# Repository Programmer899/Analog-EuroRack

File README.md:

# Analog-EuroRack
### - Description
This is an analog eurorack where you can direct signals from one module to the next and by that, produce sound.
This ia a project I have been working on for a Music project for a thing called [Half Life](https://halflife.hackclub.com).
I wanted to do something interresting, a way that you could create your own unique sound rather than writing it with code.

### - What is the meaning
The meaning for this project is that you can redirect signals from different connections and in the end get your own uniquely modulated sound. Because I have tried to have it as a "EuroRack Format" it means that in the future if I keep working on this project, I could add more modulators such as low and high pass filters, reverb, distortion, and plenty more.

### - What does this project do
This project's purpose is to allow the user to create their own sound by own taste.

### - Problems along the way
With this project it is mostly one combine problem that I have had. When trying to wire the cables and components on my PCB I struggled to fit everything in a compact area. This lead to me having cables delivering differnt signals across each other on 2 different layers and it beeing so tight that, wanting to move a single cable could include you having to move a few more components to make room in a safe way.

---

### - Schematic
The schematic might look a bit messed and stuff beeing all over but I tried to make it simple to follow. To the left I have the main component, a **SSI2130** and it's purpose is simply taking all of the different parameters and values, combining them and produce custom sounds out.

### - PCB
The PCB in other hand might be a bit more complex trying to understand.
The main part is that the SSI2130 sits in the middle and acting as the main component. To it there are capacitors, resistors, audio jacks and potentiometers connected, allowing the user to customize the sound to their own likings. Some potentiometers control the pitch of the outcoming sound and connecting to one of the 4 upper right audio jacks on the schematic gives you different sound waves such as Triangle, Sine, Square and Saw.

The pin sockets on the image are going to be either a potentiometer or an audio socket connected via cables. Needed some sort of convenient through holes to solder the cables into when building.

---
### - Build Of Materials
| Item                     | Qty | Supplier   | Cost/item | Total Cost | link                                    |
|--------------------------|-----|------------|-----------|------------|-----------------------------------------|
|                          |     |            |           |            |                                         |
| TOTAL                    |     |            |           | $0         |                                         |

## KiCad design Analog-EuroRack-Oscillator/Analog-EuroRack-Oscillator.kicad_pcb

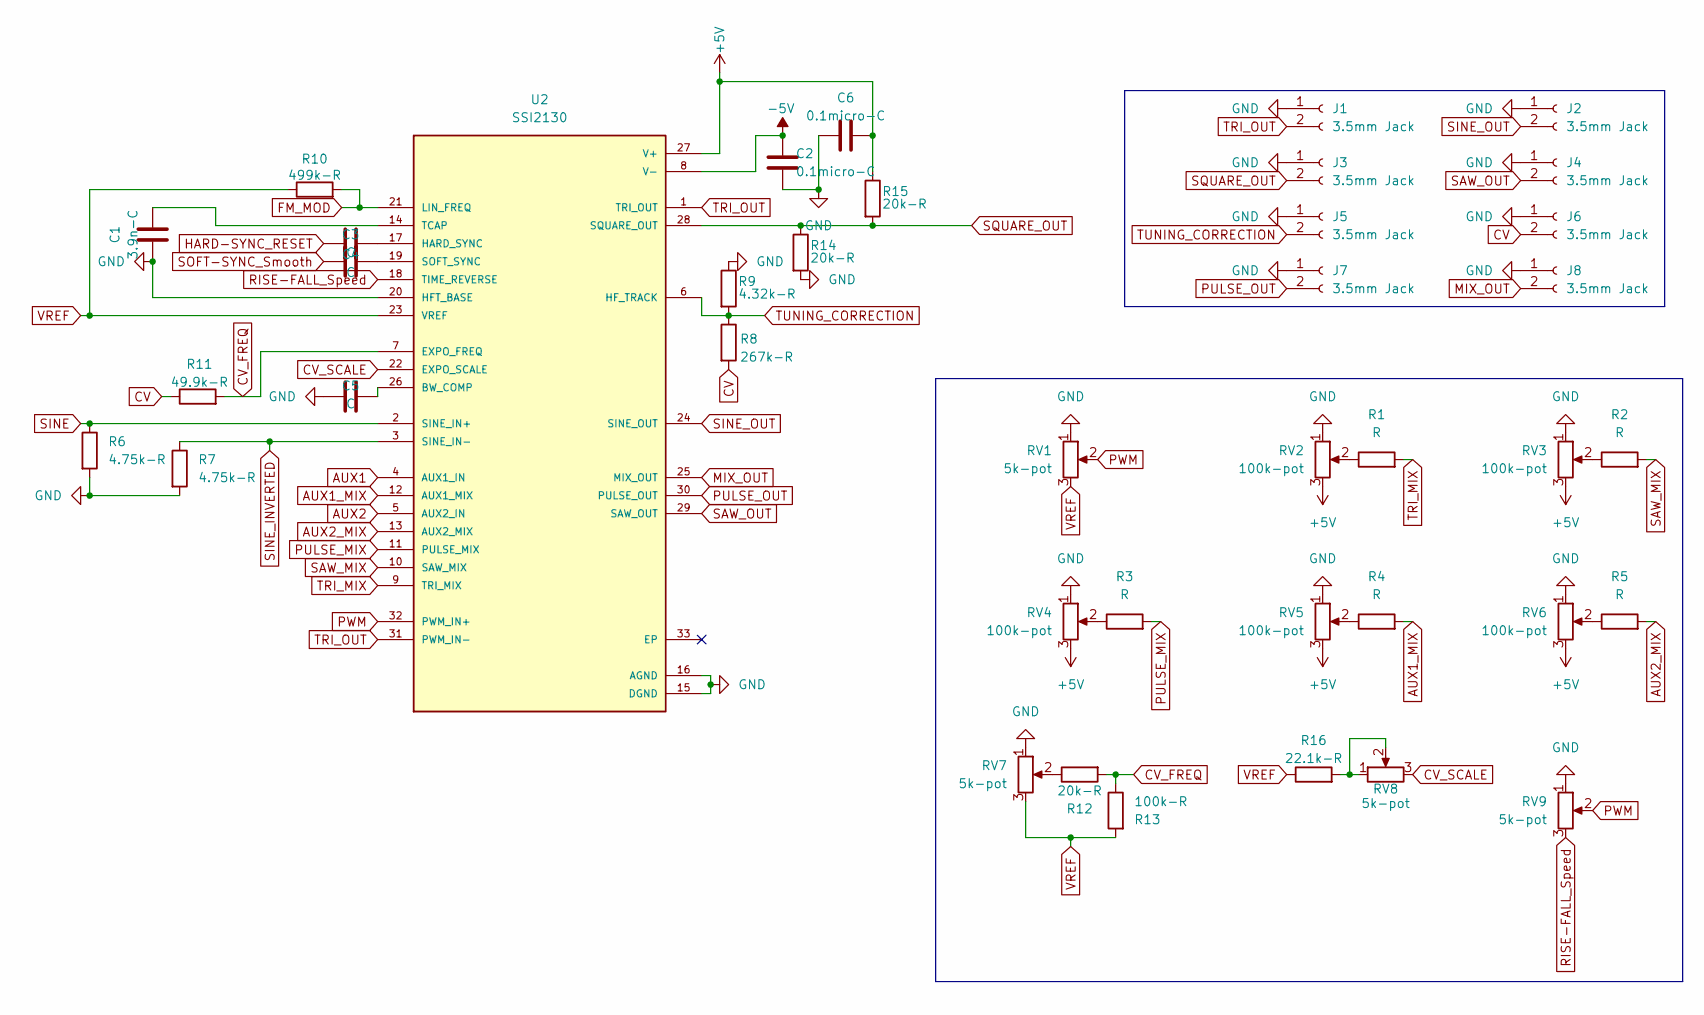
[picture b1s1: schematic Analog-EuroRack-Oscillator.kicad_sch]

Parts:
C1: 3.9n-C; CP_Radial_D5.0mm_P2.00mm
C2, C6: 0.1micro-C; CP_Radial_D5.0mm_P2.00mm
C3, C4, C5: C; CP_Radial_D5.0mm_P2.00mm
J1, J2, J3, J4, J5, J6, J7, J8: 3.5mm Jack; PinSocket_1x02_P2.54mm_Vertical
R1, R2, R3, R4, R5: R; R_Axial_DIN0207_L6.3mm_D2.5mm_P10.16mm_Horizontal
R6, R7: 4.75k-R; R_Axial_DIN0207_L6.3mm_D2.5mm_P10.16mm_Horizontal
R8: 267k-R; R_Axial_DIN0207_L6.3mm_D2.5mm_P10.16mm_Horizontal
R9: 4.32k-R; R_Axial_DIN0207_L6.3mm_D2.5mm_P10.16mm_Horizontal
R10: 499k-R; R_Axial_DIN0207_L6.3mm_D2.5mm_P10.16mm_Horizontal
R11: 49.9k-R; R_Axial_DIN0207_L6.3mm_D2.5mm_P10.16mm_Horizontal
R12, R14, R15: 20k-R; R_Axial_DIN0207_L6.3mm_D2.5mm_P10.16mm_Horizontal
R13: 100k-R; R_Axial_DIN0207_L6.3mm_D2.5mm_P10.16mm_Horizontal
R16: 22.1k-R; R_Axial_DIN0207_L6.3mm_D2.5mm_P10.16mm_Horizontal
RV1, RV7, RV8, RV9: 5k-pot; PinSocket_1x03_P2.54mm_Vertical
RV2, RV3, RV4, RV5, RV6: 100k-pot; PinSocket_1x03_P2.54mm_Vertical
U2: SSI2130; QFN40P400X400X90-33N; PARTREV Rev. 2.4

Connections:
+5V: C6.2, R15.1, RV2.3, RV3.3, RV4.3, RV5.3, RV6.3, U2.27 (V+)
-5V: C2.1, U2.8 (V-)
AUX1: U2.4 (AUX1_IN)
AUX1_MIX: R4.2, U2.12 (AUX1_MIX)
AUX2: U2.5 (AUX2_IN)
AUX2_MIX: R5.2, U2.13 (AUX2_MIX)
CV: J6.2, R8.2, R11.1
CV_FREQ: R11.2, R12.2, R13.1, U2.7 (EXPO_FREQ)
CV_SCALE: RV8.3, U2.22 (EXPO_SCALE)
FM_MOD: R10.2, U2.21 (LIN_FREQ)
GND: C1.2, C2.2, C5.2, C6.1, J1.1, J2.1, J3.1, J4.1, J5.1, J6.1, J7.1, J8.1, R6.2, R7.2, R9.1, R14.2, RV1.1, RV2.1, RV3.1, RV4.1, RV5.1, RV6.1, RV7.1, RV9.1, U2.15 (DGND), U2.16 (AGND), U2.20 (HFT_BASE)
HARD-SYNC_RESET: C3.2
MIX_OUT: J8.2, U2.25 (MIX_OUT)
unnamed: R1.1, RV2.2
unnamed: R2.1, RV3.2
unnamed: R3.1, RV4.2
unnamed: R4.1, RV5.2
unnamed: R5.1, RV6.2
unnamed: R12.1, RV7.2
unnamed: R16.2, RV8.1, RV8.2
unnamed: C5.1, U2.26 (BW_COMP)
unnamed: C3.1, U2.17 (HARD_SYNC)
unnamed: C4.1, U2.19 (SOFT_SYNC)
unnamed: C1.1, U2.14 (TCAP)
PULSE_MIX: R3.2, U2.11 (PULSE_MIX)
PULSE_OUT: J7.2, U2.30 (PULSE_OUT)
PWM: RV1.2, RV9.2, U2.32 (PWM_IN+)
RISE-FALL_Speed: RV9.3, U2.18 (TIME_REVERSE)
SAW_MIX: R2.2, U2.10 (SAW_MIX)
SAW_OUT: J4.2, U2.29 (SAW_OUT)
SINE: R6.1, U2.2 (SINE_IN+)
SINE_INVERTED: R7.1, U2.3 (SINE_IN-)
SINE_OUT: J2.2, U2.24 (SINE_OUT)
SOFT-SYNC_Smooth: C4.2
SQUARE_OUT: J3.2, R14.1, R15.2, U2.28 (SQUARE_OUT)
TRI_MIX: R1.2, U2.9 (TRI_MIX)
TRI_OUT: J1.2, U2.1 (TRI_OUT), U2.31 (PWM_IN-)
TUNING_CORRECTION: J5.2, R8.1, R9.2, U2.6 (HF_TRACK)
VREF: R10.1, R13.2, R16.1, RV1.3, RV7.3, U2.23 (VREF)

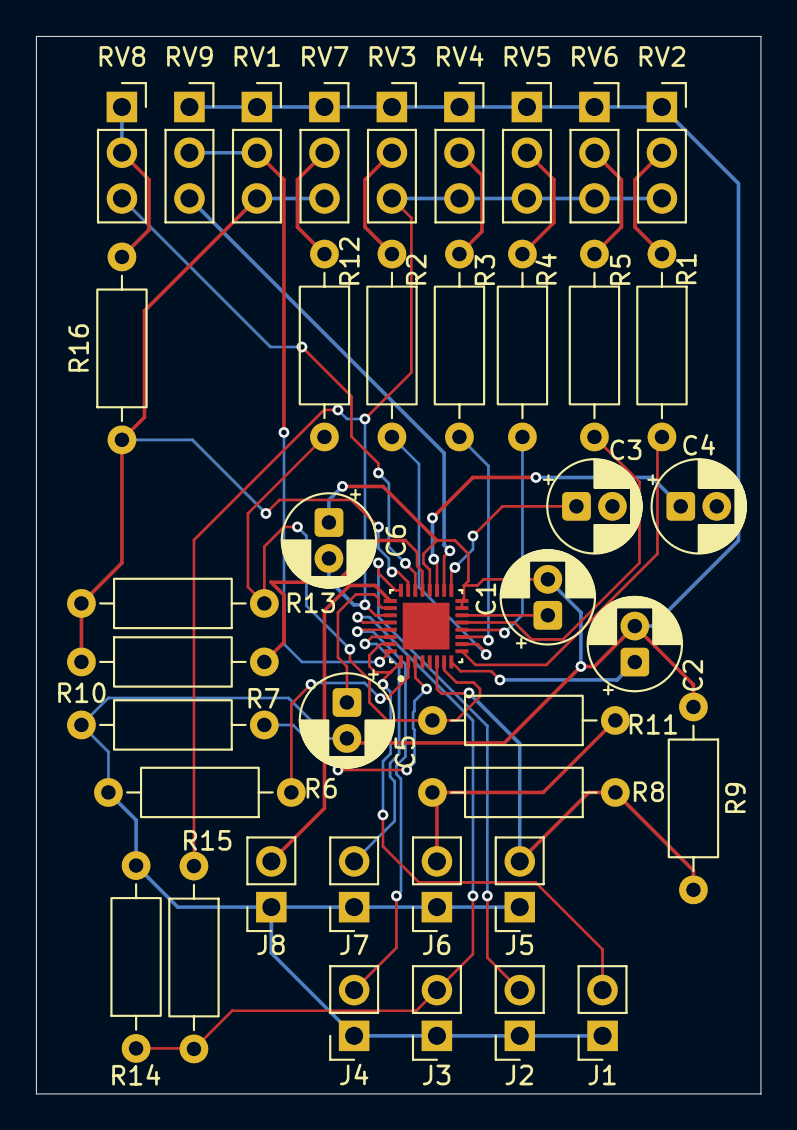
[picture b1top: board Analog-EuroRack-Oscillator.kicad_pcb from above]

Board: 2 copper layers, 40.2 x 58.8 mm, 40 parts (0 on the bottom side), 35 nets.
